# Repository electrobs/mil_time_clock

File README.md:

# Military Time Clock

Military Time Clock using the 89S51 microcontroller.

author: Jay Convertino

date: 2022.12.11

license: MIT (software/hardware)

IMPORTANT: No build instructions are included. All parts needed are here, you're on your own.

## Release Versions
### Current
  - v1.0.2 = Fixed time base issues with a smaller range tuning cap.

### Past
  - v1.0.1 = Sound buzz fixed with feedback bypass resistor.
  - v1.0.0 = Original Version

## Requirements
### Hardware
  - KiCad (v7.X.X)

### Software
  - sdcc compiler (4.0.0 #11528)

## Information

### Directory Listing:

  - docs
    - Datasheets: Data documents for various ICs.
    - Manual: User manual for the clock.
  - schematic: KiCad schematic of Military Time Clock, including PCB design and bill of materials.
  - model
    - FreeCAD: Any FreeCAD models used in the project.
    - Inventor: Any Autodesk Inventor 2023 models used in the project (STL included).
  - src: Any source code for the project.
    - clock_sdcc: contains make file and code for the clock project.

### Usage
  Please see the user manual on how to use the project. Build instructions really depend on how you want to build it. It uses all through hole parts and could be done with something as simple as an etch kit, PCB mill, or a PCB fab.

### Tuning
  Recommend using a platic tuning tool to adjust trimmer cap. Track the freqency at the 2.048kHz and lower pins till they all match there expected outputs (all powers of two, 1024, 512, 128 etc). Also let the device run for about 15 minutes and check. Frequency will rise by 1 to 2 hz and then stablize within the first 30 seconds, but it is wise to triple check after some time has passed.

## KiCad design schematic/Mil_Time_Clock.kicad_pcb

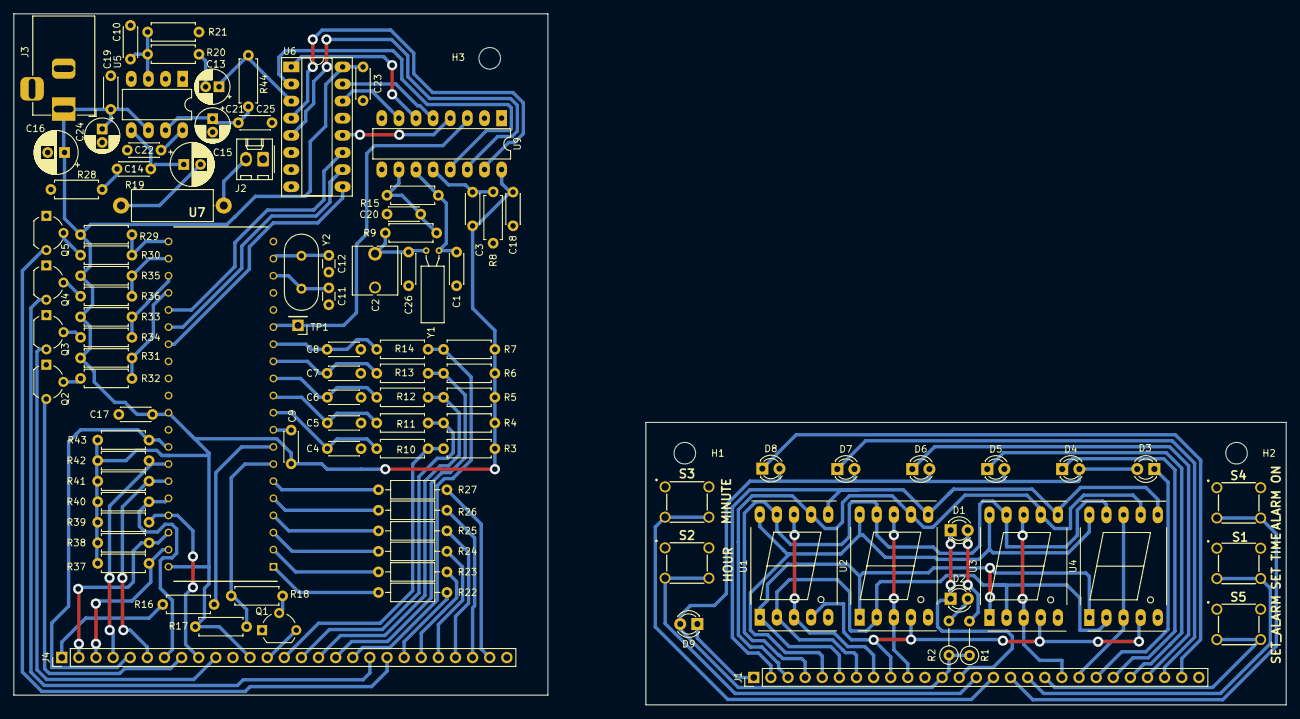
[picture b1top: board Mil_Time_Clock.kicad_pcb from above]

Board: 2 copper layers, 188.8 x 102.5 mm, 107 parts (0 on the bottom side), 84 nets.

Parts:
C1: 47pF; C_Disc_D4.3mm_W1.9mm_P5.00mm
C2: 2-5pF; C_Rect_L7.0mm_W6.5mm_P5.00mm
C3, C4, C5, C6, C7, C8, C9, C10, C17, C18, C19, C22, C23, C25: 100nF; C_Disc_D4.3mm_W1.9mm_P5.00mm
C11, C12: 18pF; C_Disc_D3.0mm_W1.6mm_P2.50mm
C13: 4.7uF; CP_Radial_D5.0mm_P2.00mm
C14: 47nF; C_Disc_D4.3mm_W1.9mm_P5.00mm
C15, C16: 330uF; CP_Radial_D6.3mm_P2.50mm
C20: 1nF; C_Disc_D4.3mm_W1.9mm_P5.00mm
C21: 47uF; CP_Radial_D5.0mm_P2.00mm
C24: 10uF; CP_Radial_D5.0mm_P2.00mm
C26: 8pF; C_Disc_D4.3mm_W1.9mm_P5.00mm
D1, D2, D3, D4, D5, D6, D7, D8, D9: LED; LED_D3.0mm
H1, H2, H3: MountingHole; MountingHole_3.2mm_M3
J1, J4: Conn_01x27; PinHeader_1x27_P2.54mm_Vertical
J2: Speaker_Conn_01x02; Molex_KK-254_AE-6410-02A_1x02_P2.54mm_Vertical
J3: Barrel_Jack_Switch; BarrelJack_Horizontal
Q1, Q2, Q3, Q4, Q5: 2N3904; TO-92_Wide
R1, R2: 1K; R_Axial_DIN0207_L6.3mm_D2.5mm_P5.08mm_Vertical
R3, R4, R5, R6, R7: 4k7; R_Axial_DIN0207_L6.3mm_D2.5mm_P7.62mm_Horizontal
R8, R18, R30, R32, R34, R36: 1k; R_Axial_DIN0207_L6.3mm_D2.5mm_P7.62mm_Horizontal
R9: 200k; R_Axial_DIN0207_L6.3mm_D2.5mm_P7.62mm_Horizontal
R10, R11, R12, R13, R14, R21, R44: 470R; R_Axial_DIN0207_L6.3mm_D2.5mm_P7.62mm_Horizontal
R15: 10M; R_Axial_DIN0207_L6.3mm_D2.5mm_P7.62mm_Horizontal
R16: 1K; R_Axial_DIN0207_L6.3mm_D2.5mm_P7.62mm_Horizontal
R17, R20, R29, R31, R33, R35: 10K; R_Axial_DIN0207_L6.3mm_D2.5mm_P7.62mm_Horizontal
R19: 8R_OPT; R_Axial_DIN0414_L11.9mm_D4.5mm_P15.24mm_Horizontal
R22, R23, R24, R25, R26, R27: 1K; R_Axial_DIN0207_L6.3mm_D2.5mm_P10.16mm_Horizontal
R28: 10R; R_Axial_DIN0207_L6.3mm_D2.5mm_P7.62mm_Horizontal
R37, R38, R39, R40, R41, R42, R43: 100R; R_Axial_DIN0207_L6.3mm_D2.5mm_P7.62mm_Horizontal
S1: SET TIME; B3F1000
S2: HOUR; B3F1000
S3: MINUTE; B3F1000
S4: ALARM ON; B3F1000
S5: SET_ALARM; B3F1000
TP1: TestPoint; PinHeader_1x01_P2.54mm_Vertical
U1, U2, U3, U4: SM420561N; 7SegmentLED_LTS6760_LTS6780
U5: LM386; DIP-8_W7.62mm_LongPads
U6: 74HC4051; DIP-16_W7.62mm_Socket_LongPads
U7: AT89S51-24PU; DIP1556W56P254L5232H483Q40N
U9: SN74HC4060N; DIP-16_W7.62mm_LongPads
Y1: 32.768Khz; Crystal_C38-LF_D3.0mm_L8.0mm_Horizontal
Y2: 12Mhz; Crystal_HC49-U_Vertical

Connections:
/LED_DISPLAY_BOARD/A: J1.3, U1.7 (A), U2.7 (A), U3.7 (A), U4.7 (A)
/LED_DISPLAY_BOARD/AL: D9.1 (K), J1.1, J4.1, R16.1
/LED_DISPLAY_BOARD/AS: J1.16, J4.16, R5.1, R12.1, S4.3, S4.4
/LED_DISPLAY_BOARD/B: J1.2, U1.6 (B), U2.6 (B), U3.6 (B), U4.6 (B)
/LED_DISPLAY_BOARD/C: J1.9, U1.4 (C), U2.4 (C), U3.4 (C), U4.4 (C)
/LED_DISPLAY_BOARD/D: J1.7, U1.2 (D), U2.2 (D), U3.2 (D), U4.2 (D)
/LED_DISPLAY_BOARD/DL: D1.1 (K), D2.1 (K), J1.13, J4.13, Q1.3 (C)
/LED_DISPLAY_BOARD/E: J1.6, U1.1 (E), U2.1 (E), U3.1 (E), U4.1 (E)
/LED_DISPLAY_BOARD/F: J1.4, U1.9 (F), U2.9 (F), U3.9 (F), U4.9 (F)
/LED_DISPLAY_BOARD/G: J1.5, U1.10 (G), U2.10 (G), U3.10 (G), U4.10 (G)
/LED_DISPLAY_BOARD/HS: J1.14, J4.14, R3.1, R10.1, S2.3, S2.4
/LED_DISPLAY_BOARD/L0: D3.1 (K), J1.21, J4.21, R22.1
/LED_DISPLAY_BOARD/L1: D4.1 (K), J1.22, J4.22, R23.1
/LED_DISPLAY_BOARD/L2: D5.1 (K), J1.23, J4.23, R24.1
/LED_DISPLAY_BOARD/L3: D6.1 (K), J1.24, J4.24, R25.1
/LED_DISPLAY_BOARD/L4: D7.1 (K), J1.25, J4.25, R26.1
/LED_DISPLAY_BOARD/L5: D8.1 (K), J1.26, J4.26, R27.1
/LED_DISPLAY_BOARD/MS: J1.15, J4.15, R4.1, R11.2, S3.3, S3.4
/LED_DISPLAY_BOARD/ONE_H: J1.10, J4.10, Q3.3 (C), U2.3 (CC), U2.8 (CC)
/LED_DISPLAY_BOARD/ONE_M: J1.20, J4.20, Q5.3 (C), U4.3 (CC), U4.8 (CC)
/LED_DISPLAY_BOARD/SAS: J1.18, J4.18, R7.1, R14.1, S5.3, S5.4
/LED_DISPLAY_BOARD/TEN_H: J1.8, J4.8, Q2.3 (C), U1.3 (CC), U1.8 (CC)
/LED_DISPLAY_BOARD/TEN_M: J1.19, J4.19, Q4.3 (C), U3.3 (CC), U3.8 (CC)
/LED_DISPLAY_BOARD/TS: J1.17, J4.17, R6.1, R13.1, S1.3, S1.4
/MCU_BOARD/A: J4.3, R37.1, U7.39 (P0.0_(AD0))
/MCU_BOARD/B: J4.2, R38.1, U7.38 (P0.1_(AD1))
/MCU_BOARD/C: J4.9, R39.1, U7.37 (P0.2_(AD2))
/MCU_BOARD/D: J4.7, R40.1, U7.36 (P0.3_(AD3))
/MCU_BOARD/E: J4.6, R41.1, U7.35 (P0.4_(AD4))
/MCU_BOARD/F: J4.4, R42.1, U7.34 (P0.5_(AD5))
/MCU_BOARD/G: J4.5, R43.1, U7.33 (P0.6_(AD6))
/MCU_BOARD/Q3: U6.14 (A1), U9.7 (QD)
/MCU_BOARD/Q4: U6.15 (A2), U9.5 (QE)
/MCU_BOARD/Q5: U6.12 (A3), U9.4 (QF)
/MCU_BOARD/Q6: U6.1 (A4), U9.6 (QG)
/MCU_BOARD/Q7: U6.5 (A5), U9.14 (QH)
/MCU_BOARD/Q8: U6.2 (A6), U9.13 (QI)
/MCU_BOARD/Q9: U6.4 (A7), U9.15 (QJ)
GND: C1.1, C2.1, C4.2, C5.2, C6.2, C7.2, C8.2, C10.2, C11.1, C12.2, C16.2, C17.2, C18.2, C19.2, C20.1, C21.2, C22.1, C23.2, C24.2, C25.2, C26.2, J1.27, J2.1, J3.2, J3.3, J4.27, Q1.1 (E), Q2.1 (E), Q3.1 (E), Q4.1 (E), Q5.1 (E), R8.2, R21.1, R28.2, S1.1, S1.2, S2.1, S2.2, S3.1, S3.2, S4.1, S4.2, S5.1, S5.2, U5.2 (-), U5.4 (GND), U6.6 (~E), U6.7 (VEE), U6.8 (GND), U6.13 (A0), U7.20 (GND), U9.8 (GND)
unnamed: C2.2, C26.1, R9.1, Y1.1
unnamed: C13.2, R20.2
unnamed: C14.1, C15.1, U5.5
unnamed: C14.2, R28.1
unnamed: C15.2, R19.2
unnamed: C22.2, U5.8 (GAIN)
unnamed: D1.2 (A), R1.2
unnamed: D2.2 (A), R2.2
unnamed: J2.2, R19.1
unnamed: Q1.2 (B), R18.2
unnamed: Q2.2 (B), R32.2
unnamed: Q3.2 (B), R34.2
unnamed: Q4.2 (B), R36.2
unnamed: Q5.2 (B), R30.2
unnamed: C10.1, R20.1, R21.2, U5.3 (+)
unnamed: C21.1, C25.1, R44.1, U5.7 (BYPASS)
unnamed: C13.1, R44.2, U6.3 (A)
unnamed: U6.11 (S0), U7.25 (P2.4_(A12))
unnamed: U6.10 (S1), U7.26 (P2.5_(A13))
unnamed: U6.9 (S2), U7.27 (P2.6_(A14))
unnamed: R17.2, R18.1, U7.7 ((MISO)_P1.6)
unnamed: R27.2, U7.6 ((MOSI)_P1.5)
unnamed: C4.1, R10.2, U7.10 ((RXD)_P3.0)
unnamed: R16.2, U7.8 ((SCK)_P1.7)
unnamed: C8.1, R14.2, U7.14 ((T0)_P3.4)
unnamed: TP1.1, U7.15 ((T1)_P3.5), U9.3 (QN)
unnamed: C5.1, R11.1, U7.11 ((TXD)_P3.1)
unnamed: C6.1, R12.2, U7.12 ((~INT0)_P3.2)
unnamed: C7.1, R13.2, U7.13 ((~INT1)_P3.3)
unnamed: R22.2, U7.1 (P1.0)
unnamed: R23.2, U7.2 (P1.1)
unnamed: R24.2, U7.3 (P1.2)
unnamed: R25.2, U7.4 (P1.3)
unnamed: R26.2, U7.5 (P1.4)
unnamed: R29.1, R30.1, U7.21 (P2.0_(A8))
unnamed: R35.1, R36.1, U7.22 (P2.1_(A9))
unnamed: R33.1, R34.1, U7.23 (P2.2_(A10))
unnamed: R31.1, R32.1, U7.24 (P2.3_(A11))
unnamed: C9.2, U7.9 (RST)
unnamed: C12.1, U7.19 (XTAL1), Y2.1
unnamed: C11.2, U7.18 (XTAL2), Y2.2
unnamed: C1.2, R15.2, U9.11 (CLKI), Y1.2
unnamed: C3.2, R8.1, U9.12 (CLR)
unnamed: C20.2, R9.2, R15.1, U9.10 (~CLKO)
VCC: C3.1, C9.1, C16.1, C17.1, C18.1, C19.1, C23.1, C24.1, D3.2 (A), D4.2 (A), D5.2 (A), D6.2 (A), D7.2 (A), D8.2 (A), D9.2 (A), J1.12, J3.1, J4.12, R1.1, R2.1, R3.2, R4.2, R5.2, R6.2, R7.2, R17.1, R29.2, R31.2, R33.2, R35.2, R37.2, R38.2, R39.2, R40.2, R41.2, R42.2, R43.2, U5.6 (V+), U6.16 (VCC), U7.31 (~EA/VPP), U7.40 (VCC), U9.16 (VCC)

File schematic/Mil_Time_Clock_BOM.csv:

Date:,Tue 27 Dec 2022 05:07:47 PM EST,,,,,,,,
Component Count:,102,,,,,,,,
,,,,,,,,,
Collated Components:,,,,,,,,,
,,,,,,,,,
Item,Qty,Reference(s),Value,Datasheet,Supplier,Manufacturer,Manufacturer Part Number,Price (Each @1),Price (@ Quantity)
CAP CER 47PF 100V C0G RADIAL,1,C1,47pF,https://product.tdk.com/en/system/files?file=dam/doc/product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,Digikey,TDK,FG28C0G2A470JNT00,$0.27,$0.27
CAP TRIMMER 6.5-30PF 100V TH,1,C2,6-30pF,https://media.digikey.com/pdf/Data%20Sheets/EW%20Electronics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,Digikey,EW Electronics,GKG30015,$0.97,$0.97
CAP CER 0.1UF 100V X7S RADIAL,14,"C3, C4, C5, C6, C7, C8, C9, C10, C17, C18, C19, C22, C23, C25",100nF,https://product.tdk.com/en/system/files?file=dam/doc/product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,Digkey,TDK,FG28X7S2A104KRT06,$0.38,$5.32
CAP CER 18PF 100V C0G/NP0 RADIAL,2,"C11, C12",18pF,https://datasheets.kyocera-avx.com/SR-Series.pdf,Digkey,KYOCERA AVX,SR151A180JAR,$0.52,$1.04
CAP ALUM 4.7UF 20% 16V RADIAL,1,C13,4.7uF,https://www.mouser.com/datasheet/2/212/KEM_A4004_ESK-1103206.pdf,Digikey,Kemet,ESK475M016AC3AA,$0.24,$0.24
CAP CER 47PF 100V C0G RADIAL,1,C14,47nF,https://product.tdk.com/en/system/files?file=dam/doc/product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,Digkey,TDK,FG28C0G2A470JNT06,$0.27,$0.27
CAP ALUM 330UF 20% 6.3V RADIAL,2,"C15, C16",330uF,https://www.mouser.com/datasheet/2/212/KEM_A4004_ESK-1103206.pdf,Digikey,Kemet,ESK337M6R3AE3AA,$0.27,$0.54
CAP CER 1000PF 100V X7R RADIAL,1,C20,1nF,https://product.tdk.com/en/system/files?file=dam/doc/product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,Digkey,TDK,FG28X7R2A102KNT06,$0.27,$0.27
CAP ALUM 47UF 20% 6.3V RADIAL,1,C21,47uF,https://www.mouser.com/datasheet/2/212/KEM_A4004_ESK-1103206.pdf,Digikey,Kemet,ESK476M6R3AC3AA,$0.22,$0.22
CAP ALUM 10UF 20% 16V RADIAL,1,C24,10uF,https://www.mouser.com/datasheet/2/212/KEM_A4004_ESK-1103206.pdf,Digikey,Kemet,ESK106M016AC3KA,$0.24,$0.24
CAP CER 18PF 100V C0G RADIAL,1,C26,18pF,https://product.tdk.com/en/system/files?file=dam/doc/product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,Digikey,TDK,FG28C0G2A180JNT00,$0.29,$0.29
LED GREEN DIFFUSED 3MM ROUND T/H,9,"D1, D2, D3, D4, D5, D6, D7, D8, D9",LED,https://www.we-online.com/components/products/datasheet/1510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,Digikey,Würth Elektronik,151031VS06000,$0.17,$1.53
CONN HEADER R/A 36POS 2.54MM (CUT TO LENGTH),1,"J1, J4 (BOTH ARE SAME PART, BOARD TO BOARD CONNECT)",Conn_01x27,https://multimedia.3m.com/mws/media/22446O/3mtm-100-in-pinst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,Digikey,3M,929500-01-36-RK,$3.52,$3.52
0.1W Round Ferrite Speaker,1,J2 – Speaker,Speaker_Conn,https://www.jameco.com/z/45P30S-Panasonic-0-1W-Round-Ferrite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,Jameco,Panasonic,45P30S,$0.69,$0.69
DC Power Connectors Power Jack/Connector 2.1mm x 5.5mm,1,J3,Barrel_Jack_Switch,https://www.gravitech.us/poja2x51.html,Mouser,Gravitech,CON-SOCJ-2155,$1.00,$1.00
TRANS NPN 40V 0.2A TO92-3,5,"Q1, Q2, Q3, Q4, Q5",2N3904,https://www.onsemi.com/pdf/datasheet/pzt3904-d.pdf,Digikey,onsemi,2N3904TFR,$0.38,$1.90
RES 1K OHM 5% 1/4W AXIAL,2,"R1, R2",1K,https://www.te.com/commerce/DocumentDelivery/DDEController?A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,Digikey,TE Connectivity Passive Product,CFR16J1K0,$0.10,$0.20
RES 4K7 OHM 5% 1/4W AXIAL,5,"R3, R4, R5, R6, R7",4k7,https://www.te.com/commerce/DocumentDelivery/DDEController?A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,Digikey,TE Connectivity Passive Product,CFR16J4K7,$0.10,$0.50
RES 1K OHM 5% 1/4W AXIAL,6,"R8, R18, R30, R32, R34, R36",1k,https://www.te.com/commerce/DocumentDelivery/DDEController?A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,Digikey,TE Connectivity Passive Product,CFR16J1K0,$0.10,$0.60
RES 200K OHM 5% 1/4W AXIAL,1,R9,200k,https://www.seielect.com/catalog/sei-cf_cfm.pdf,Digikey,Stackpole Electronics Inc,CF14JT200K,$0.10,$0.10
RES 470 OHM 5% 1/4W AXIAL,6,"R10, R11, R12, R13, R14, R21",470R,https://www.te.com/commerce/DocumentDelivery/DDEController?A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,Digikey,TE Connectivity Passive Product,CFR16J470R,$0.10,$0.60
RES 10M OHM 5% 1/4W AXIAL,1,R15,10M,https://www.seielect.com/catalog/sei-cf_cfm.pdf,Digikey,Stackpole Electronics Inc,CF14JT10M0,$0.10,$0.10
RES 1K OHM 5% 1/4W AXIAL,1,R16,1K,https://www.te.com/commerce/DocumentDelivery/DDEController?A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,Digikey,TE Connectivity Passive Product,CFR16J1K0,$0.10,$0.10
RES 10K OHM 5% 1/4W AXIAL,6,"R17, R20, R29, R31, R33, R35",10K,https://www.te.com/commerce/DocumentDelivery/DDEController?A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,Digikey,TE Connectivity Passive Product,CFR16J10K,$0.10,$0.60
RES 1K OHM 5% 1/4W AXIAL,6,"R22, R23, R24, R25, R26, R27",1K,https://www.te.com/commerce/DocumentDelivery/DDEController?A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,Digikey,TE Connectivity Passive Product,CFR16J1K0,$0.10,$0.60
RES 10 OHM 5% 1/4W AXIAL,1,R28,10R,https://www.seielect.com/catalog/sei-cf_cfm.pdf,Digikey,Stackpole Electronics Inc,CF14JT10R0,$0.10,$0.10
RES 100 OHM 5% 1/4W AXIAL,7,"R37, R38, R39, R40, R41, R42, R43",100R,https://www.te.com/commerce/DocumentDelivery/DDEController?A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,Digikey,TE Connectivity Passive Product,CFR16J100R,$0.10,$0.70
SWITCH TACTILE SPST-NO 0.05A 12V,5,"S1, S2, S3, S4, S5",SPST-NO,https://sten-eswitch-13110800-production.s3.amazonaws.com/sy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,Digikey,E-Switch,TL1105DF160Q,$0.20,$1.00
CONN HEADER VERT 1POS,1,TP1,TestPoint,Connector Header Through Hole 1 position,Digikey,Amphenol ICC,861400011YO2LF,$0.10,$0.10
7 SEGMENT LED DISPLAY,4,"U1, U2, U3, U4",SM420561N,https://www.we-online.com/components/products/datasheet/1571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,Digikey,Würth Elektronik,157142V12703,$1.09,$4.36
IC AMP CLASS AB MONO 700MW 8DIP,1,U5,LM386,http://www.ti.com/lit/ds/symlink/lm386.pdf,Digikey,Texas Instruments,LM386,$1.34,$1.34
IC MUX/DEMUX 8X1 16DIP,1,U6,74HC4051,https://www.ti.com/general/docs/suppproductinfo.tsp?distId=1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,Digikey,Texas Instruments,CD74HC4051E,$0.78,$0.78
IC MCU 8BIT 4KB FLASH 40DIP,1,U7,AT89S51-24PU,https://ww1.microchip.com/downloads/en/DeviceDoc/doc2487.pdf,Digikey,Microchip,AT89S51-24PU,$3.63,$3.63
IC ASYNC BIN CNTR/OSCIL 16 DIP,1,U9,SN74HC4060N,https://www.ti.com/general/docs/suppproductinfo.tsp?distId=1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,Digikey,Texas Instruments,SN74HC4060N,$0.85,$0.85
CRYSTAL 32.7680KHZ 12.5PF TH,1,Y1,32.768Khz,https://abracon.com/Resonators/AB38T.pdf,Digikey,Abracon,AB38T-32.768KHZ,$0.17,$0.17
CRYSTAL 12.0000MHZ 18PF TH,1,Y2,12Mhz,https://www.ctscorp.com/wp-content/uploads/ATS-ATSSM.pdf,Digikey,CTS-Frequency Control,ATS120B-E,$0.36,$0.36
AC/DC WALL MOUNT ADAPTER 5V 2.5W 2.1x5.5mm Barrel Plug,1,N/A,PSU,https://www.nteinc.com/acdc_adapters/adapters_01.pdf,Digikey,NTE,57-5D-500-4,$10.01,$10.01
,,,,,,,,,
Total Cost:,$45.11,,,,,,,,

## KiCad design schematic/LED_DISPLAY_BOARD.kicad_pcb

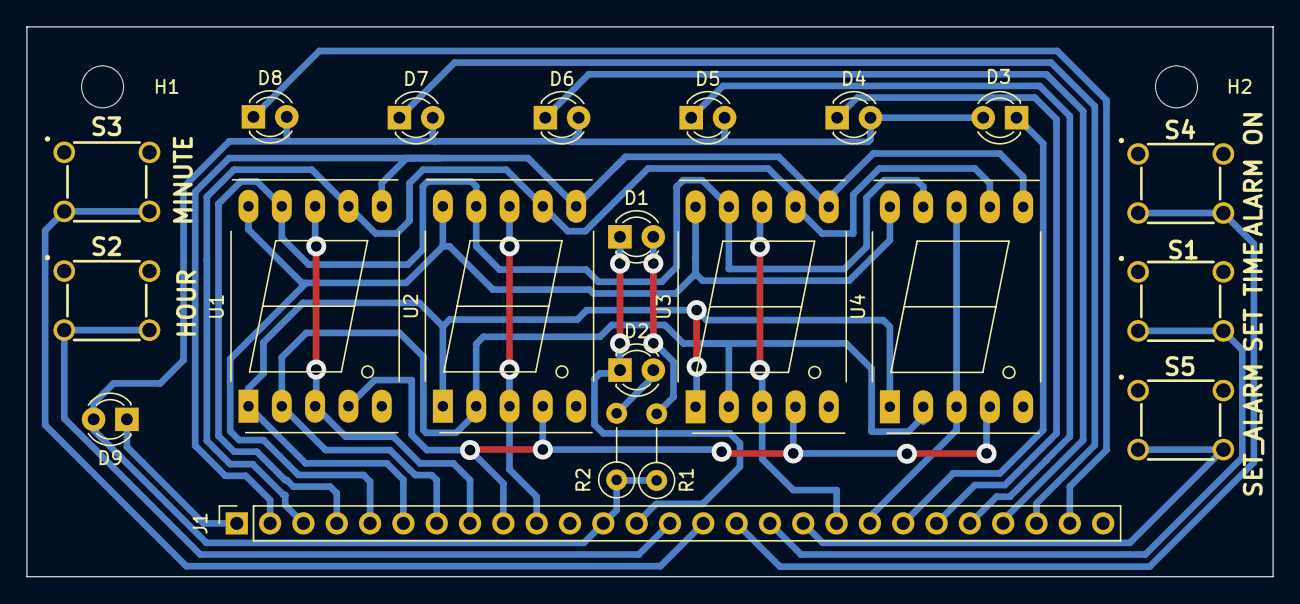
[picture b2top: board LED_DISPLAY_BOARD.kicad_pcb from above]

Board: 2 copper layers, 95.0 x 41.9 mm, 23 parts (0 on the bottom side), 28 nets.

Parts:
D1, D2, D3, D4, D5, D6, D7, D8, D9: LED; LED_D3.0mm
H1, H2: MountingHole; MountingHole_3.2mm_M3
J1: Conn_01x27; PinSocket_1x27_P2.54mm_Vertical
R1, R2: 220R; R_Axial_DIN0207_L6.3mm_D2.5mm_P5.08mm_Vertical
S1: SET TIME; B3F1000
S2: HOUR; B3F1000
S3: MINUTE; B3F1000
S4: ALARM ON; B3F1000
S5: SET_ALARM; B3F1000
U1, U2, U3, U4: SM420561N; 7SegmentLED_LTS6760_LTS6780

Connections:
/LED_DISPLAY_BOARD/A: J1.3, U1.7 (A), U2.7 (A), U3.7 (A), U4.7 (A)
/LED_DISPLAY_BOARD/AL: D9.1 (K), J1.1
/LED_DISPLAY_BOARD/AS: J1.16, S4.3, S4.4
/LED_DISPLAY_BOARD/B: J1.2, U1.6 (B), U2.6 (B), U3.6 (B), U4.6 (B)
/LED_DISPLAY_BOARD/C: J1.9, U1.4 (C), U2.4 (C), U3.4 (C), U4.4 (C)
/LED_DISPLAY_BOARD/D: J1.7, U1.2 (D), U2.2 (D), U3.2 (D), U4.2 (D)
/LED_DISPLAY_BOARD/DL: D1.1 (K), D2.1 (K), J1.13
/LED_DISPLAY_BOARD/E: J1.6, U1.1 (E), U2.1 (E), U3.1 (E), U4.1 (E)
/LED_DISPLAY_BOARD/F: J1.4, U1.9 (F), U2.9 (F), U3.9 (F), U4.9 (F)
/LED_DISPLAY_BOARD/G: J1.5, U1.10 (G), U2.10 (G), U3.10 (G), U4.10 (G)
/LED_DISPLAY_BOARD/HS: J1.14, S2.3, S2.4
/LED_DISPLAY_BOARD/L0: D3.1 (K), J1.21
/LED_DISPLAY_BOARD/L1: D4.1 (K), J1.22
/LED_DISPLAY_BOARD/L2: D5.1 (K), J1.23
/LED_DISPLAY_BOARD/L3: D6.1 (K), J1.24
/LED_DISPLAY_BOARD/L4: D7.1 (K), J1.25
/LED_DISPLAY_BOARD/L5: D8.1 (K), J1.26
/LED_DISPLAY_BOARD/MS: J1.15, S3.3, S3.4
/LED_DISPLAY_BOARD/ONE_H: J1.10, U2.3 (CC), U2.8 (CC)
/LED_DISPLAY_BOARD/ONE_M: J1.20, U4.3 (CC), U4.8 (CC)
/LED_DISPLAY_BOARD/SAS: J1.18, S5.3, S5.4
/LED_DISPLAY_BOARD/TEN_H: J1.8, U1.3 (CC), U1.8 (CC)
/LED_DISPLAY_BOARD/TEN_M: J1.19, U3.3 (CC), U3.8 (CC)
/LED_DISPLAY_BOARD/TS: J1.17, S1.3, S1.4
GND: J1.27, S1.1, S1.2, S2.1, S2.2, S3.1, S3.2, S4.1, S4.2, S5.1, S5.2
unnamed: D1.2 (A), R1.2
unnamed: D2.2 (A), R2.2
VCC: D3.2 (A), D4.2 (A), D5.2 (A), D6.2 (A), D7.2 (A), D8.2 (A), D9.2 (A), J1.12, R1.1, R2.1

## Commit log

2022-12-11 initial commit for v1.0.0
2022-12-16 updated pdf documents
2022-12-16 changed some grammer
2022-12-16 updated case for 3d printing
2022-12-21 adjusted a trace, since ISOPRO did not pick up on it being 12 mil away.
2022-12-21 whoops, wrong trace, now the 12 mil trace is adjusted
2022-12-21 changed cap values to fix issues with clock crystial, was off by +2 hz
2022-12-21 tweaked the schematic, now the trimmer cap + start value adds up to the other cap of 47 pf for balance.
2022-12-27 updated BOM with all part numbers and costs, at 5.11 they are not cheap in small runs.
2022-12-27 updated manual to reflect new cap values for clock. was sitting at 32.771k, new values bring it to 32.768k
2023-01-13 added padding resistor to halve the speaker volume and deal with some noise issues in some units. Noise is originating from the 7 segment LED data lines. It runs at about 1khz so this makes sense, wi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
2023-01-16 mit license update
2023-04-24 fixed ground issue
2023-07-18 bad state, but wanted to document changes to the v1 cap values. Need to fix PCB, it got messed up for some odd reason.
2023-07-20 added resistor from input to bypass of lm386. When the alarm is off the input is ground, this reduces noise issues to about nothing. Updated PCB.
2023-08-06 adjusted cap values for best possible +/- 3 hz adjustment around 2048 clock output. This produces the best clock so far and allows for finer tuning at the lower frequencies.
2024-03-25 fixed for github
